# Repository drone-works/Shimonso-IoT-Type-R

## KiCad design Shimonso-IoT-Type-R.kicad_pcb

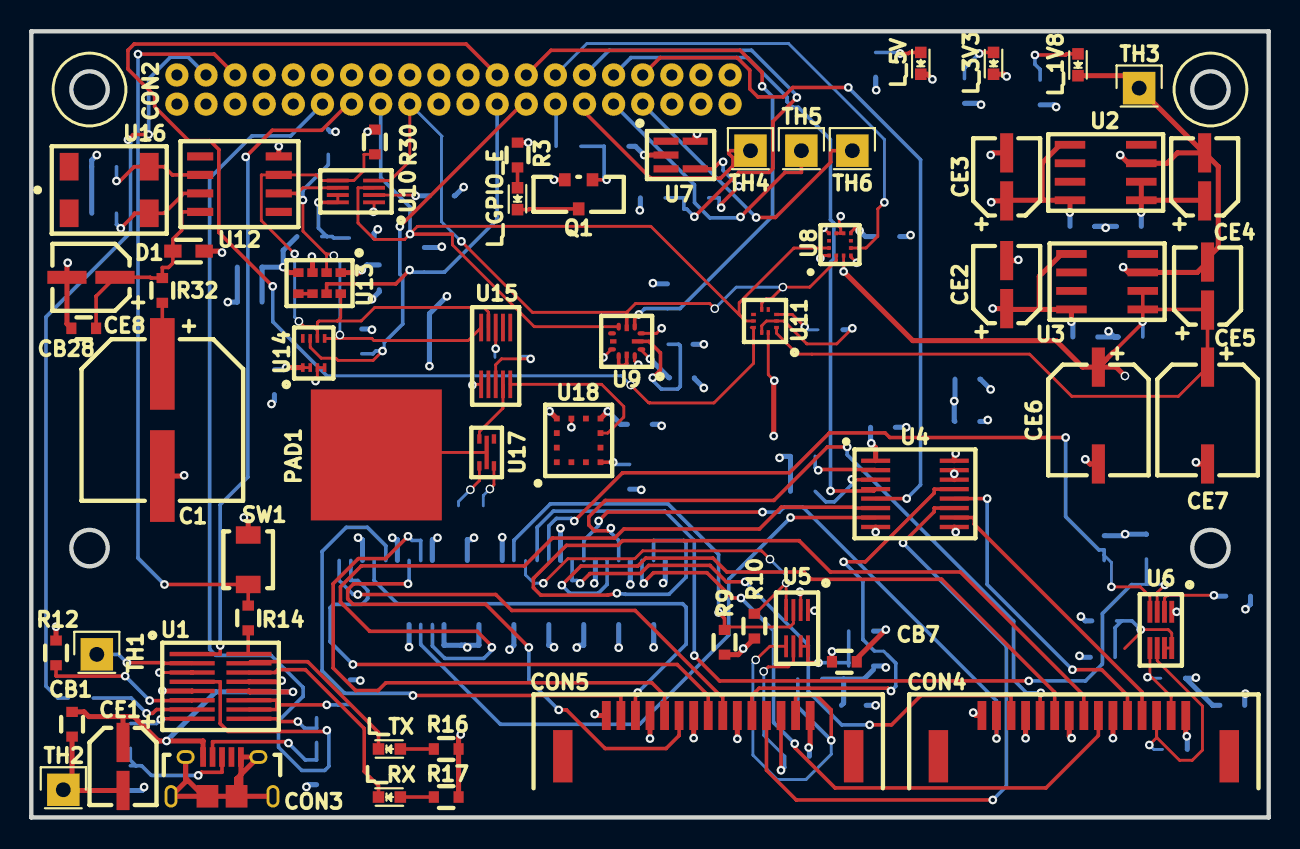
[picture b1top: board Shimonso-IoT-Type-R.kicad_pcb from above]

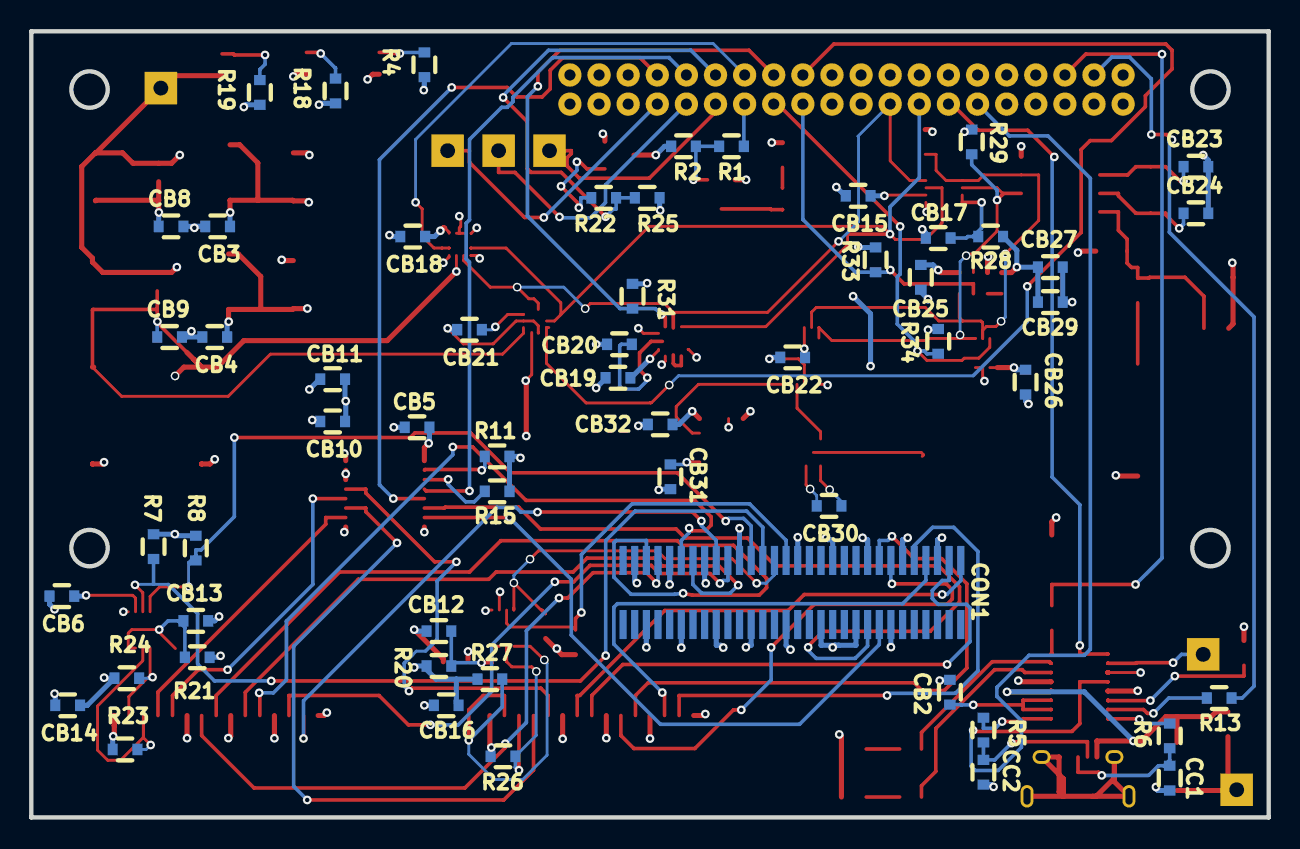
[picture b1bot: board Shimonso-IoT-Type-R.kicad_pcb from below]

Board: 4 copper layers, 85.0 x 54.0 mm, 116 parts (57 on the bottom side), 88 nets.

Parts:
C1: 3.5V0.47F; FCS0V474ZFTBR24
CB1, CB2, CB3, CB4, CB5, CB6, CB7, CB8, CB9, CB10, CB11, CB12, CB13, CB14, CB15, CB16, CB17, CB18, CB22, CB26, CB27, CB28, CB29, CB32: 104; GRM18
CB19, CB20, CB21: 1.0uF; GRM18
CB23, CB24: 0; GRM18
CB25, CB30: 10uF; GRM18
CB31: 1nF; GRM18
CC1, CC2: 39pF; GRM18
CE1: 10uF; OS-CON-A5
CE2, CE3, CE4, CE5, CE8: 22uF; OS-CON-A5
CE6, CE7: 47uF; OS-CON-C6
CON1: 96Boards_HS_connector; 61083-063402LF
CON2: 96Boards_LS_connector; conn2X20_2mm
CON3: microUSB_CONSOLE; 10118194-0001LF
CON4, CON5: CONN_01X15; 1-84952-5
D1: D; 1SS355
LED1: L_GPIO_E; LED_1608mm
LED2: L_5V; LED_1608mm
LED3: L_3V3; LED_1608mm
LED4: L_1V8; LED_1608mm
LED5: L_TX; LED_1608mm
LED6: L_RX; LED_1608mm
PAD1: PAD
Q1: S8050; MMSS8050
R1, R2, R13, R14, R16, R17, R18: 220; MCR03
R3: 390; MCR03
R4: 620; MCR03
R5, R6: 22; MCR03
R7, R8, R9, R10, R11, R15, R23, R24, R26, R27, R29, R30: 2.2k; MCR03
R12: 10K; MCR03
R19: 160; MCR03
R20, R21, R28: 200k; MCR03
R22: 18k; MCR03
R25: 10k; MCR03
R31, R33, R34: 4.7k; MCR03
R32: 1k; MCR03
SW1: RST; B3U-1000P
TH1, TH2, TH3, TH4, TH5, TH6: TH
U1: FT230X; FT230XS
U2: BD33GC0WEFJ; BDxxGC0WEFJ
U3: BD18GC0WEFJ; BDxxGC0WEFJ
U4: SN74AVC4T245; SN74AVC4T245PWT
U5, U6, U10: PCA9306DC1
U7: bd7411g; BD7411G
U8: kx022-1020; KX022-1020
U9: bm1383glv; BM1383GLV
U11: bm1422gmv; BM1422GMV
U12: BU9873; BU9873F-GTE2
U13: rpr-0521rs; RPR-0521RS
U14: bh1745nuc; BH1745NUC
U15: ADS1115
U16: MC-306_32.768K-E3; MC-306
U17: BD1020HFV; BD1020HFV_test
U18: ML8511A

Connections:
/1V8: CB5.1, CB6.1, CB7.1, CB9.1, CB15.1, CB18.1, CB19.1, CE5.1, CE6.1, CE7.1, R7.1, R8.1, R9.1, R10.1, R11.1, R15.1, R19.1, R31.1, R33.1, R34.1, U1.3, U3.1, U3.2, U4.1, U5.2, U6.2, U8.3, U8.7, U8.10, U9.2, U10.2, U11.1, U11.10
/3V3: CB8.1, CB10.1, CB11.1, CB14.1, CB16.1, CB22.1, CB25.1, CB26.1, CB27.1, CB29.1, CB30.1, CB32.1, CE4.1, CON4.15, CON5.15, D1.2, R16.1, R17.1, R18.1, R20.1, R21.1, R23.1, R24.1, R26.1, R27.1, R28.1, R29.1, R30.1, U2.1, U2.2, U4.16, U13.1, U13.4, U14.1, U14.2, U15.1, U15.8, U17.4, U18.4, U18.7
/5V: CB3.1, CB4.1, CE2.1, CE3.1, CON2.37, R3.1, R4.1, U2.5, U2.8, U3.5, U3.8, U7.5
/+5F: CB1.1, CE1.1, CON3.1, U1.12
/BD7411G_OUT_1V8: CON2.30, R22.1, R25.1
/BD7411G_OUT_5V: R22.2, U7.4
/BH1745NUC_INT: CON2.25, R34.2, U14.7
/BM1383GLV_INT: CON2.26, R31.2, U9.11
/BM1422GMV_DRDY: CON2.24, U11.8
/CAM1_CLK: CON1.17, U4.6
/CAM1_CLK_3V3: CON5.12, U4.11
/CAM1_GPIO: CON2.32, U4.4
/CAM1_GPIO_3V3: CON5.11, U4.13
/CAM2_CLK: CON1.15, U4.7
/CAM2_CLK_3V3: CON4.12, U4.10
/CAM2_GPIO: CON2.34, U4.5
/CAM2_GPIO_3V3: CON4.11, U4.12
/CSI0_CLK_N: CON1.4, CON5.8
/CSI0_CLK_P: CON1.2, CON5.9
/CSI0_DATA0_N: CON1.10, CON5.2
/CSI0_DATA0_P: CON1.8, CON5.3
/CSI0_DATA1_N: CON1.16, CON5.5
/CSI0_DATA1_P: CON1.14, CON5.6
/CSI1_CLK_N: CON1.56, CON4.8
/CSI1_CLK_P: CON1.54, CON4.9
/CSI1_DATA0_N: CON1.44, CON4.2
/CSI1_DATA0_P: CON1.42, CON4.3
/CSI1_DATA1_N: CON1.50, CON4.5
/CSI1_DATA1_P: CON1.48, CON4.6
/EXP_RSTOUT_N: CON2.6, R14.1, SW1.1
/I2C0_SCL: CON2.15, U8.12, U9.9, U10.3, U11.7
/I2C0_SCL_3V3: R29.2, U10.6, U12.2, U13.2, U14.5, U15.10
/I2C0_SDA: CON2.17, U8.2, U9.10, U10.4, U11.5
/I2C0_SDA_3V3: R30.2, U10.5, U12.3, U13.8, U14.6, U15.9
/ISP0_SCL: CON1.32, R9.2, U5.3
/ISP0_SCL_3V3: CON5.13, R26.2, U5.6
/ISP0_SDA: CON1.34, R10.2, U5.4
/ISP0_SDA_3V3: CON5.14, R27.2, U5.5
/ISP1_SCL: CON1.36, R7.2, U6.3
/ISP1_SCL_3V3: CON4.13, R23.2, U6.6
/ISP1_SDA: CON1.38, R8.2, U6.4
/ISP1_SDA_3V3: CON4.14, R24.2, U6.5
/KX022-1020_INT1: CON2.28, U8.5
/PMU_PWRON_N: CON2.4, R13.1
/RPR-0521RS_INT: CON2.23, R33.2, U13.7
/UART3_RX: CON2.13, U1.1
/UART3_TX: CON2.11, U1.4
/USBDM: CC2.1, CON3.2, R5.2
/USBDP: CC1.1, CON3.3, R6.2
GND: C1.2, CB1.2, CB2.2, CB3.2, CB4.2, CB5.2, CB6.2, CB7.2, CB8.2, CB9.2, CB10.2, CB11.2, CB12.2, CB13.2, CB14.2, CB15.2, CB16.2, CB17.2, CB18.2, CB19.2, CB20.2, CB21.2, CB22.2, CB23.2, CB24.2, CB25.2, CB26.2, CB27.2, CB28.2, CB29.2, CB30.2, CB31.2, CB32.2, CC1.2, CC2.2, CE1.2, CE2.2, CE3.2, CE4.2, CE5.2, CE6.2, CE7.2, CE8.2, CON1.6, CON1.12, CON1.13, CON1.18, CON1.19, CON1.24, CON1.25, CON1.30, CON1.31, CON1.37, CON1.40, CON1.43, CON1.46, CON1.49, CON1.52, CON1.55, CON1.58, CON2.1, CON2.2, CON2.39, CON2.40, CON3.5, CON3.6, CON3.7, CON3.8, CON3.9, CON3.10, CON3.11, CON4.1, CON4.4, CON4.7, CON4.10, CON5.1, CON5.4, CON5.7, CON5.10, LED2.1, LED3.1, LED4.1, Q1.1, R2.1, R12.1, R25.2, SW1.2, TH2.1, TH3.1, U1.5, U1.13, U2.3, U3.3, U4.8, U4.9, U4.14, U4.15, U5.1, U6.1, U7.2, U8.1, U8.4, U8.8, U8.9, U9.3, U9.6, U9.12, U10.1, U11.2, U11.9, U12.4, U13.3, U14.3, U14.4, U15.3, U17.5, U18.5
unnamed: C1.1, R32.1
unnamed: CB2.1, U1.10, U1.11
unnamed: CB12.1, R20.2, U5.7, U5.8
unnamed: CB13.1, R21.2, U6.7, U6.8
unnamed: CB17.1, R28.2, U10.7, U10.8
unnamed: CB20.1, U9.1
unnamed: CB21.1, U11.3
unnamed: CB23.1, U12.6, U16.4
unnamed: CB24.1, U12.7, U16.1
unnamed: CB28.1, CE8.1, D1.1, R32.2, U12.8
unnamed: CB31.1, U18.10
unnamed: CON2.27, R1.2
unnamed: CON2.29, TH4.1
unnamed: CON2.31, TH5.1
unnamed: CON2.33, TH6.1
unnamed: LED1.1, Q1.3
unnamed: LED1.2, R3.2
unnamed: LED2.2, R4.2
unnamed: LED3.2, R18.2
unnamed: LED4.2, R19.2
unnamed: LED5.1, U1.15
unnamed: LED5.2, R16.2
unnamed: LED6.1, U1.14
unnamed: LED6.2, R17.2
unnamed: PAD1.1, U17.2
unnamed: Q1.2, R1.1, R2.2
unnamed: R5.1, U1.9
unnamed: R6.1, U1.8
unnamed: R11.2, U4.2
unnamed: R12.2, U1.6
unnamed: R13.2, U1.7
unnamed: R14.2, U1.16
unnamed: R15.2, U4.3
unnamed: TH1.1, U1.2
unnamed: U9.4, U9.5
unnamed: U13.5, U13.6
unnamed: U15.4, U17.3
unnamed: U15.5, U18.8

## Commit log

2016-05-21 Second commit
2016-05-22 Add a LSConnectorlib to droneworks.lib
2016-05-22 Add name of camera connectors.
2016-05-22 Change connections of CAM_GPIO.
2016-05-22 Change parts of LS_Connector. Rev 0.03
2016-05-22 Change parts of HS connector Rev 0.04
2016-05-22 Add LEDs and a reset button.
2016-05-22 Add LEDs for LDO Rev 0.06
2016-05-22 Add KX022-1020 foot print
2016-05-23 Add a footprint of BM1745GLV
2016-05-23 Change a footprint BM1383GLV
2016-05-24 Change text
2016-05-24 Add a footprint of BM1422GMV
2016-05-24 Add a footprint of RPR-0521RS
2016-05-24 Add a footprint of BH1745NUC
2016-05-24 Add a footprint of BD7411G
2016-05-26 Add comments Rev 0.08
2016-05-27 Add footprints of BD1020HFV and BDxxGC0WEFJ
2016-05-29 Modified footprints
2016-05-29 Add a footprint of ADS1115
2016-05-30 Add a footprint of BU9873F-GTE2
2016-05-31 Add a footprint of PCA9306DC1
2016-06-08 Add footprints
2016-06-08 Add CSI connector
2016-06-14 Add footpronts of LSconnector and MC-306
2016-06-21 Add footprints of transistor, PAD and Diode.
2016-06-21 Initial commit for pcb file
2016-06-22 modified
2016-06-25 placement modified
2016-07-11 DRC_ok
2016-08-10 Add outputdata directory
2016-08-10 modified outputdata
2016-08-10 modified coodinate axis
2016-08-15 change to autorout pcb
